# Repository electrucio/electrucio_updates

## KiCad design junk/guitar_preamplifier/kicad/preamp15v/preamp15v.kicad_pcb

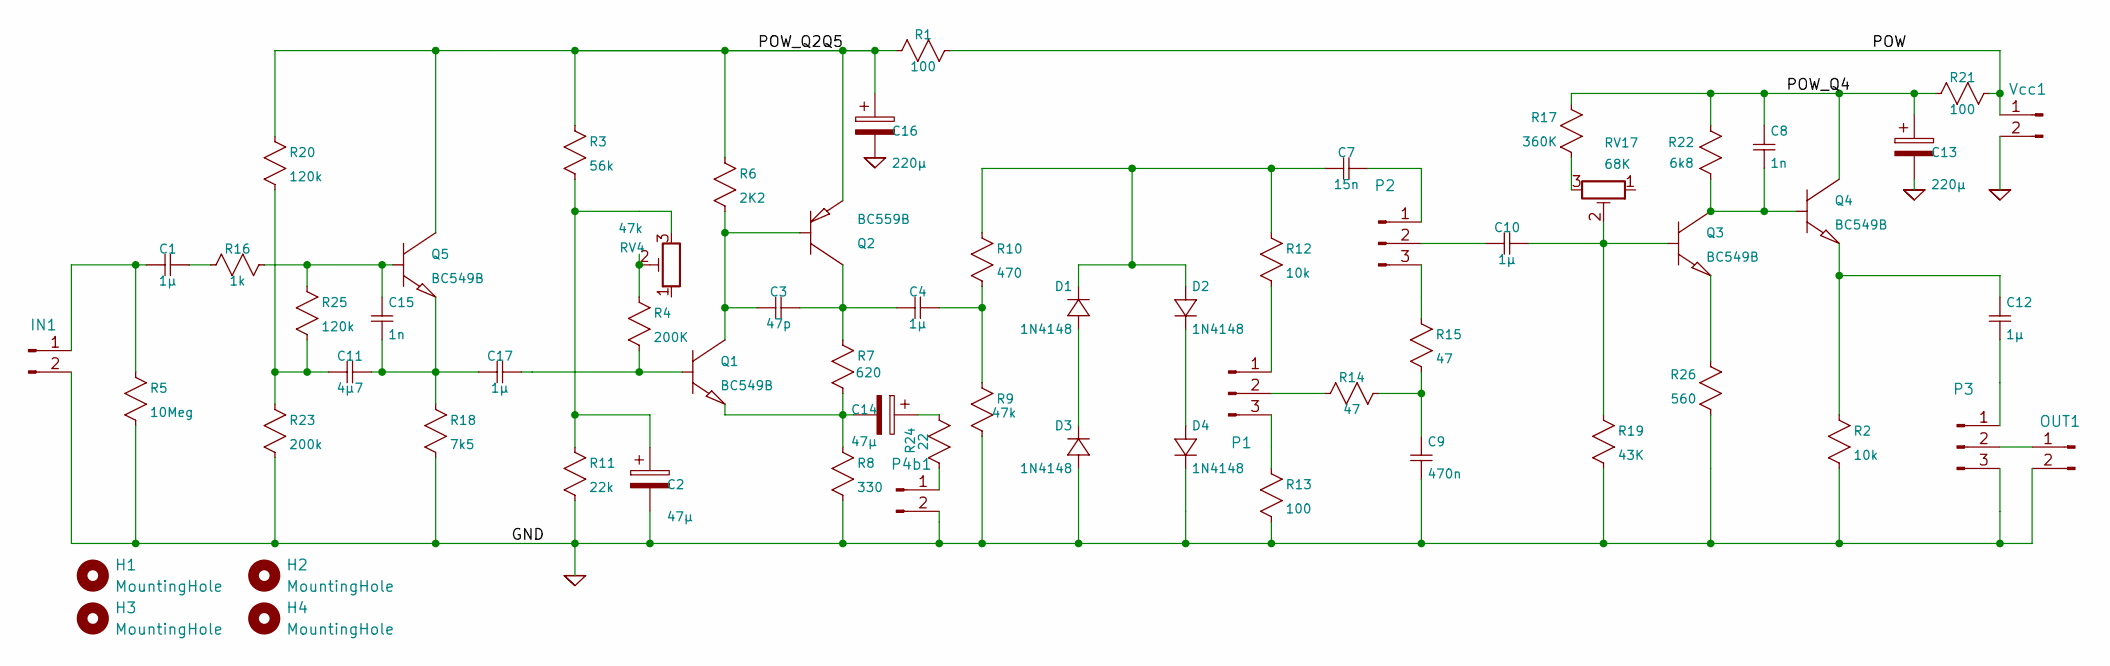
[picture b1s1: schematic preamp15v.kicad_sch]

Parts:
C1, C4, C10, C12, C17: 1µ; C_Rect_WIMA_1uF_CNC_LargePads
C2, C14: 47µ; CP_Radial_D5.0mm_P2.00mm_largerpads
C3: 47p; C_Disc_D4.3mm_W1.9mm_P5.00mm_largerpads
C7: 15n; C_Rect_L13.0mm_W4.0mm_P10.00mm_FKS3_FKP3_MKS4
C8, C15: 1n; C_Rect_WIMA_1uF_CNC_LargePads
C9: 470n; C_Rect_L26.5mm_W10.5mm_P22.50mm_MKS4
C11: 4µ7; CP_Radial_D5.0mm_P2.00mm_largerpads
C13, C16: 220µ; CP_Radial_220u_8mm_3.5mm_largerpads
D1, D2, D3, D4: 1N4148; D_DO-35_SOD27_P7.62mm_Horizontal_largerpads
H1, H2, H3, H4: MountingHole; MountingHole_3.5mm
IN1: JST_XH_B2B-XH-A_1x02_P2.50mm_Vertical_ovalpads
OUT1: JST_XH_B2B-XH-A_1x02_P2.50mm_Vertical_ovalpads
P1, P2, P3: JST_XH_B3B-XH-A_1x03_P2.50mm_Vertical_ovalpads
P4b1: JST_XH_B2B-XH-A_1x02_P2.50mm_Vertical_ovalpads
Q1, Q3, Q4, Q5: BC549B; TO-92_Inline_Wide_largerpads
Q2: BC559B; TO-92_Inline_Wide_largerpads
R1, R13, R21: 100; R_Axial_DIN0207_L6.3mm_D2.5mm_P10.16mm_Horizontal_LargerPads
R2, R12: 10k; R_Axial_DIN0207_L6.3mm_D2.5mm_P10.16mm_Horizontal_LargerPads
R3: 56k; R_Axial_DIN0207_L6.3mm_D2.5mm_P10.16mm_Horizontal_LargerPads
R4: 200K; R_Axial_DIN0207_L6.3mm_D2.5mm_P10.16mm_Horizontal_LargerPads
R5: 10Meg; R_Axial_DIN0207_L6.3mm_D2.5mm_P10.16mm_Horizontal_LargerPads
R6: 2K2; R_Axial_DIN0207_L6.3mm_D2.5mm_P10.16mm_Horizontal_LargerPads
R7: 620; R_Axial_DIN0207_L6.3mm_D2.5mm_P10.16mm_Horizontal_LargerPads
R8: 330; R_Axial_DIN0207_L6.3mm_D2.5mm_P10.16mm_Horizontal_LargerPads
R9: 47k; R_Axial_DIN0207_L6.3mm_D2.5mm_P10.16mm_Horizontal_LargerPads
R10: 470; R_Axial_DIN0207_L6.3mm_D2.5mm_P10.16mm_Horizontal_LargerPads
R11: 22k; R_Axial_DIN0207_L6.3mm_D2.5mm_P10.16mm_Horizontal_LargerPads
R14, R15: 47; R_Axial_DIN0207_L6.3mm_D2.5mm_P10.16mm_Horizontal_LargerPads
R16: 1k; R_Axial_DIN0207_L6.3mm_D2.5mm_P10.16mm_Horizontal_LargerPads
R17: 360K; R_Axial_DIN0207_L6.3mm_D2.5mm_P10.16mm_Horizontal_LargerPads
R18: 7k5; R_Axial_DIN0207_L6.3mm_D2.5mm_P10.16mm_Horizontal_LargerPads
R19: 43K; R_Axial_DIN0207_L6.3mm_D2.5mm_P10.16mm_Horizontal_LargerPads
R20, R25: 120k; R_Axial_DIN0207_L6.3mm_D2.5mm_P10.16mm_Horizontal_LargerPads
R22: 6k8; R_Axial_DIN0207_L6.3mm_D2.5mm_P10.16mm_Horizontal_LargerPads
R23: 200k; R_Axial_DIN0207_L6.3mm_D2.5mm_P10.16mm_Horizontal_LargerPads
R24: 22; R_Axial_DIN0207_L6.3mm_D2.5mm_P10.16mm_Horizontal_LargerPads
R26: 560; R_Axial_DIN0207_L6.3mm_D2.5mm_P10.16mm_Horizontal_LargerPads
RV4: 47k; Potentiometer_Piher_PT-6-V_Vertical_largerpads
RV17: 68K; Potentiometer_Piher_PT-6-V_Vertical_largerpads
Vcc1: JST_XH_B2B-XH-A_1x02_P2.50mm_Vertical_ovalpads

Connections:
0: C2.2, C9.2, C13.2, C16.2, D3.1 (+), D4.2 (-), IN1.2, OUT1.2, P3.3, P4b1.2, R2.2, R5.2, R8.2, R9.2, R11.2, R13.2, R18.2, R19.2, R23.2, R26.1, Vcc1.2
/POW: R1.1, R21.1, Vcc1.1
/POW_Q2Q5: C16.1, Q2.3 (E), Q5.1 (C), R1.2, R3.1, R6.1, R20.1
/POW_Q4: C8.1, C13.1, Q4.1 (C), R17.2, R21.2, R22.1
unnamed: C1.1, R16.2
unnamed: C2.1, R3.2, R11.1, RV4.3
unnamed: C4.1, R9.1, R10.2
unnamed: C9.1, R14.1, R15.2
unnamed: C11.2, R20.2, R23.1, R25.2
unnamed: C14.1, R24.2
unnamed: D1.1 (+), D3.2 (-)
unnamed: C7.2, D1.2 (-), D2.1 (+), R10.1, R12.1
unnamed: D2.2 (-), D4.1 (+)
unnamed: C1.2, IN1.1, R5.1
unnamed: OUT1.1, P3.2
unnamed: P1.1, R12.2
unnamed: P1.2, R14.2
unnamed: P1.3, R13.1
unnamed: C7.1, P2.1
unnamed: C10.2, P2.2
unnamed: P2.3, R15.1
unnamed: C12.2, P3.1
unnamed: P4b1.1, R24.1
unnamed: C17.1, Q1.2 (B), R4.2
unnamed: C3.2, Q1.1 (C), Q2.2 (B), R6.2
unnamed: C14.2, Q1.3 (E), R7.2, R8.1
unnamed: C3.1, C4.2, Q2.1 (C), R7.1
unnamed: C10.1, Q3.2 (B), R19.1, RV17.2
unnamed: C8.2, Q3.1 (C), Q4.2 (B), R22.2
unnamed: Q3.3 (E), R26.2
unnamed: C12.1, Q4.3 (E), R2.1
unnamed: C15.1, Q5.2 (B), R16.1, R25.1
unnamed: C11.1, C15.2, C17.2, Q5.3 (E), R18.1
unnamed: R4.1, RV4.2
unnamed: R17.1, RV17.3

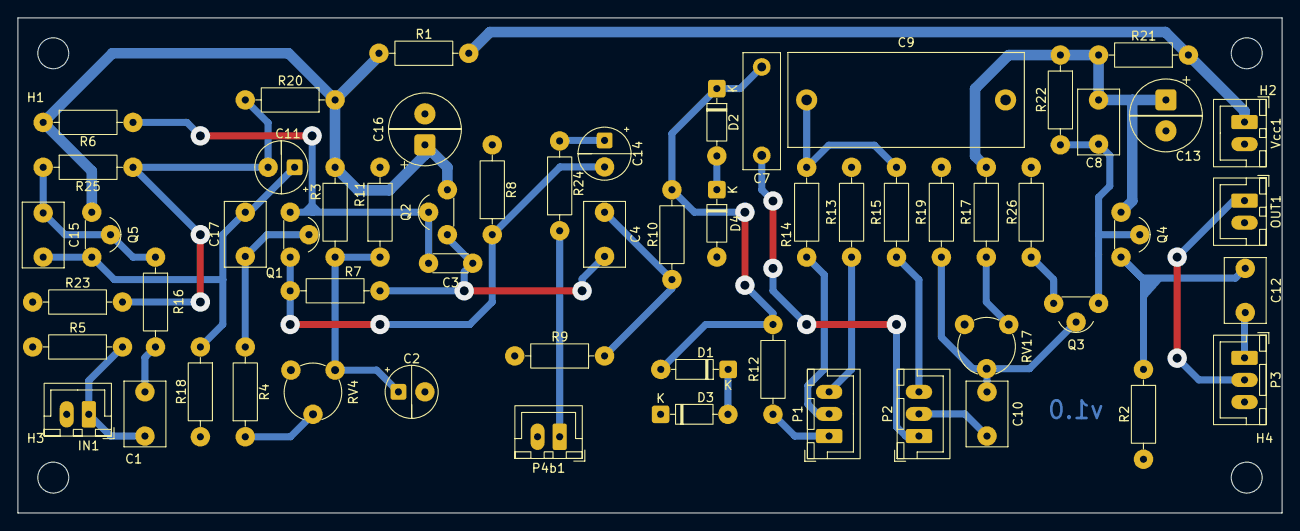
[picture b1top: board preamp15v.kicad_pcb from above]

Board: 2 copper layers, 143.0 x 56.0 mm, 63 parts (0 on the bottom side), 35 nets.

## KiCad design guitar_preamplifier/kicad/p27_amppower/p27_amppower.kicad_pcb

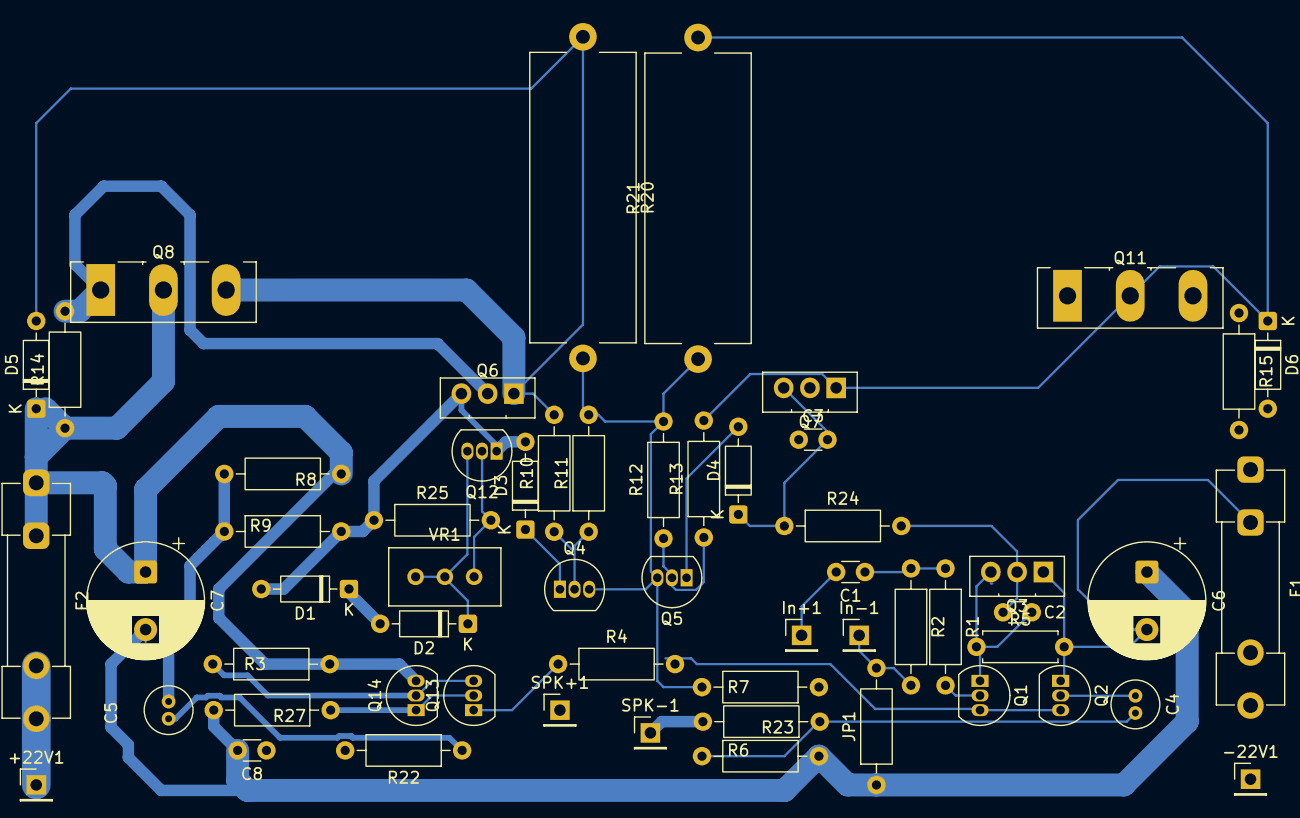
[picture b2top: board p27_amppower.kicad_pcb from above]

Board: 2 copper layers, 58 parts (0 on the bottom side), 33 nets.

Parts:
+22V1: Conn_01x01_Pin; PinHeader_1x01_P2.54mm_Vertical
-22V1: Conn_01x01_Pin; PinHeader_1x01_P2.54mm_Vertical
C1: 1µ; C_Disc_D3.0mm_W1.6mm_P2.50mm
C2: 470p; C_Disc_D3.0mm_W1.6mm_P2.50mm
C3: 220p; C_Disc_D3.0mm_W1.6mm_P2.50mm
C4, C5: 22µ; C_Radial_D4.0mm_H7.0mm_P1.50mm
C6, C7: 220µ; CP_Radial_D10.0mm_P5.00mm
C8: 100n; C_Disc_D3.0mm_W1.6mm_P2.50mm
D1, D2, D3, D4, D5, D6: D; D_DO-35_SOD27_P7.62mm_Horizontal
F1, F2: 3A; Fuseholder_Clip-5x20mm_Littelfuse_100_Inline_P20.50x4.60mm_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
In+1: Conn_01x01_Pin; PinHeader_1x01_P2.54mm_Vertical
In-1: Conn_01x01_Pin; PinHeader_1x01_P2.54mm_Vertical
JP1: Jumper_2_Open; R_Axial_DIN0207_L6.3mm_D2.5mm_P10.16mm_Horizontal
Q1, Q2, Q5, Q13, Q14: BC556; TO-92_Inline
Q3, Q6: BD139; TO-126-3_Vertical
Q4, Q12: BC546; TO-92_Inline
Q7: BD140; TO-126-3_Vertical
Q8: TIP36C; TO-247-3_Vertical
Q11: TIP35C; TO-247-3_Vertical
R1, R8, R9, R25: 2k2; R_Axial_DIN0207_L6.3mm_D2.5mm_P10.16mm_Horizontal
R2, R7, R27: 22k; R_Axial_DIN0207_L6.3mm_D2.5mm_P10.16mm_Horizontal
R3: 270; R_Axial_DIN0207_L6.3mm_D2.5mm_P10.16mm_Horizontal
R4, R6: 1k; R_Axial_DIN0207_L6.3mm_D2.5mm_P10.16mm_Horizontal
R5: 330; R_Axial_DIN0207_L6.3mm_D2.5mm_P7.62mm_Horizontal
R10, R13, R14, R15: 560; R_Axial_DIN0207_L6.3mm_D2.5mm_P10.16mm_Horizontal
R11, R12: 820; R_Axial_DIN0207_L6.3mm_D2.5mm_P10.16mm_Horizontal
R20, R21: 0R22; R_Axial_Power_L25.0mm_W9.0mm_P27.94mm
R22: 2R7; R_Axial_DIN0207_L6.3mm_D2.5mm_P10.16mm_Horizontal
R23, R24: 100; R_Axial_DIN0207_L6.3mm_D2.5mm_P10.16mm_Horizontal
SPK+1: Conn_01x01_Pin; PinHeader_1x01_P2.54mm_Vertical
SPK-1: Conn_01x01_Pin; PinHeader_1x01_P2.54mm_Vertical
VR1: 5k; Potentiometer_Bourns_3296W_Vertical

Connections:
GNDREF: C6.1, C7.2, C8.2, JP1.1 (A), R6.2, R27.2
unnamed: +22V1.1, F2.2
unnamed: -22V1.1, F1.2
unnamed: C1.1, R1.1, R2.1
unnamed: C4.2, R6.1, R23.1
unnamed: C5.1, R8.2, R9.1
unnamed: C8.1, R22.2
unnamed: D1.2 (A), D3.2 (A), Q6.3 (B), Q12.1 (C), R9.2, R25.1
unnamed: D1.1 (K), D2.2 (A)
unnamed: C3.2, D2.1 (K), D4.1 (K), Q7.3 (B), Q12.3 (E), R24.1, VR1.2, VR1.3
unnamed: D3.1 (K), Q4.1 (C)
unnamed: D4.2 (A), Q5.1 (C)
unnamed: D5.2 (A), Q6.1 (E), Q8.3 (E), R10.2, R20.1
unnamed: C7.1, D5.1 (K), F2.1, Q8.2 (C), Q14.3 (E), R3.1, R8.1, R14.1
unnamed: C6.2, D6.2 (A), F1.1, Q2.1 (C), Q3.1 (E), Q11.3 (E), R5.2, R15.2
unnamed: D6.1 (K), Q7.1 (E), Q11.2 (C), R13.2, R21.2
unnamed: C1.2, In+1.1
unnamed: In-1.1, JP1.2 (B), R2.2
unnamed: Q1.2 (B), R1.2
unnamed: C2.2, Q1.1 (C), Q3.3 (B), R5.1
unnamed: Q1.3 (E), Q2.3 (E), R4.2
unnamed: C4.1, Q2.2 (B), R7.1
unnamed: C2.1, Q3.2 (C), R24.2
unnamed: Q4.2 (B), R10.1, R11.1
unnamed: C5.2, Q4.3 (E), Q5.3 (E), R7.2, R11.2, R12.2, R20.2, R21.1, R22.1, SPK+1.1
unnamed: Q5.2 (B), R12.1, R13.1
unnamed: Q6.2 (C), Q8.1 (B), R14.2
unnamed: C3.1, Q7.2 (C), Q11.1 (B), R15.1
unnamed: Q12.2 (B), R25.2, VR1.1
unnamed: Q13.2 (B), Q14.1 (C), R27.1
unnamed: Q13.1 (C), R4.1
unnamed: Q13.3 (E), Q14.2 (B), R3.2
unnamed: R23.2, SPK-1.1

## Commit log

2026-03-09 First commits about guitar preamplifier project
2026-03-09 Add chat with Gemini to improve red circuits design
2026-03-11 Add .gitattributes
2026-03-11 Add .gitignore
2026-03-12 Update redesign_15v.asc and add noise analysis
2026-03-14 Attemp to fix encoding issues
2026-03-14 Replace jfet input buffer by bjt with bootstrap
2026-03-17 Add jlh1969.asc
2026-03-17 Add p27_amppower
2026-03-19 Add parse_log.py for redcircuits_design
2026-03-20 Update some files
2026-03-22 Update redesign_15v.asc with new diode clipping approach
2026-03-23 Update in redesign and jupyter notebook
2026-04-16 Add dockerfile for openems
2026-04-29 Update preamp15v
2026-05-02 Move temporary experiments to junk directory
2026-05-03 Add power_supply_unit.asc
2026-05-05 Move elcheapo to junk directory
2026-05-11 Add AudioAmpCompl-40W.asc
2026-06-14 Update guitar amplifier files
2026-06-14 Remove uneeded file
2026-06-14 Update files
2026-06-14 Add html viewer for power amp guitar amplifier
2026-06-14 Add power supply
